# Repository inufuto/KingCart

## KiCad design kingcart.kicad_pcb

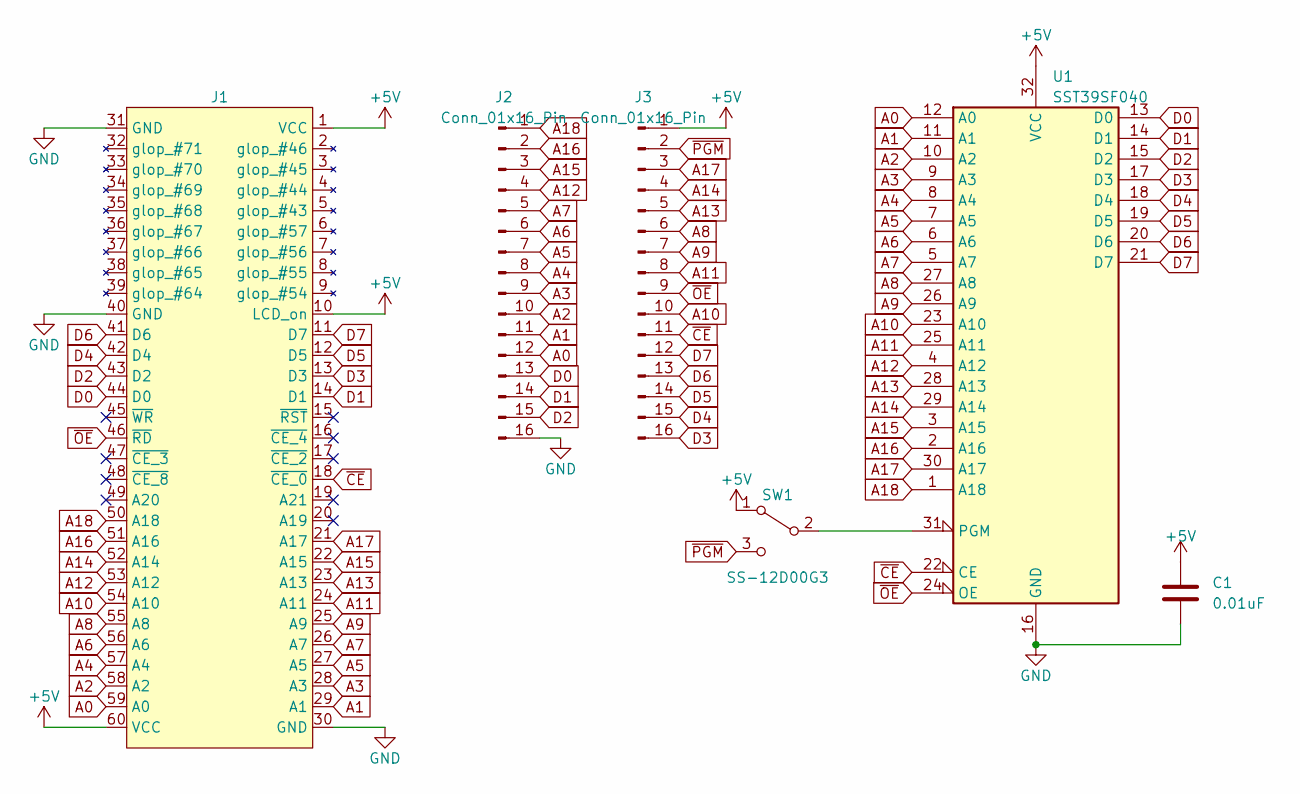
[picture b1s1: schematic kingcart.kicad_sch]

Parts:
C1: 0.01uF; C_Disc_D5.0mm_W2.5mm_P5.00mm
J1: GameKing
J2, J3: Conn_01x16_Pin; PinHeader_1x16_P2.54mm_Vertical
SW1: SS-12D00G3; SlideSW
U1: SST39SF040; PLCC-32_THT-Socket

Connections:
+5V: C1.1, J1.1 (VCC), J1.10 (LCD_on), J1.60 (VCC), J3.1, SW1.1 (A), U1.32 (VCC)
A0: J1.59 (A0), J2.12, U1.12 (A0)
A1: J1.29 (A1), J2.11, U1.11 (A1)
A2: J1.58 (A2), J2.10, U1.10 (A2)
A3: J1.28 (A3), J2.9, U1.9 (A3)
A4: J1.57 (A4), J2.8, U1.8 (A4)
A5: J1.27 (A5), J2.7, U1.7 (A5)
A6: J1.56 (A6), J2.6, U1.6 (A6)
A7: J1.26 (A7), J2.5, U1.5 (A7)
A8: J1.55 (A8), J3.6, U1.27 (A8)
A9: J1.25 (A9), J3.7, U1.26 (A9)
A10: J1.54 (A10), J3.10, U1.23 (A10)
A11: J1.24 (A11), J3.8, U1.25 (A11)
A12: J1.53 (A12), J2.4, U1.4 (A12)
A13: J1.23 (A13), J3.5, U1.28 (A13)
A14: J1.52 (A14), J3.4, U1.29 (A14)
A15: J1.22 (A15), J2.3, U1.3 (A15)
A16: J1.51 (A16), J2.2, U1.2 (A16)
A17: J1.21 (A17), J3.3, U1.30 (A17)
A18: J1.50 (A18), J2.1, U1.1 (A18)
D0: J1.44 (D0), J2.13, U1.13 (D0)
D1: J1.14 (D1), J2.14, U1.14 (D1)
D2: J1.43 (D2), J2.15, U1.15 (D2)
D3: J1.13 (D3), J3.16, U1.17 (D3)
D4: J1.42 (D4), J3.15, U1.18 (D4)
D5: J1.12 (D5), J3.14, U1.19 (D5)
D6: J1.41 (D6), J3.13, U1.20 (D6)
D7: J1.11 (D7), J3.12, U1.21 (D7)
GND: C1.2, J1.30 (GND), J1.31 (GND), J1.40 (GND), J2.16, U1.16 (GND)
unnamed: SW1.2 (B), U1.31 (PGM)
~CE: J1.18 (~CE_0), J3.11, U1.22 (CE)
~OE: J1.46 (~RD), J3.9, U1.24 (OE)
~PGM: J3.2, SW1.3 (C)

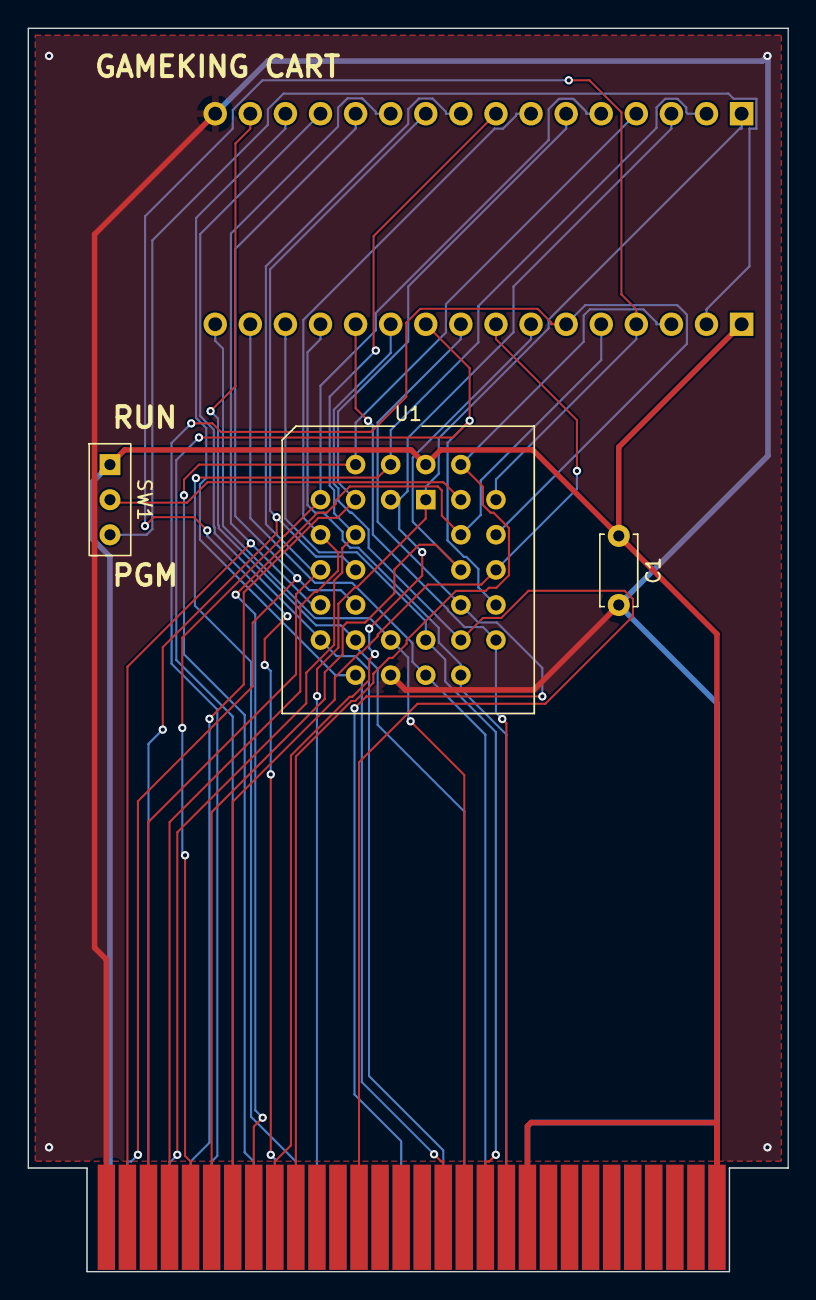
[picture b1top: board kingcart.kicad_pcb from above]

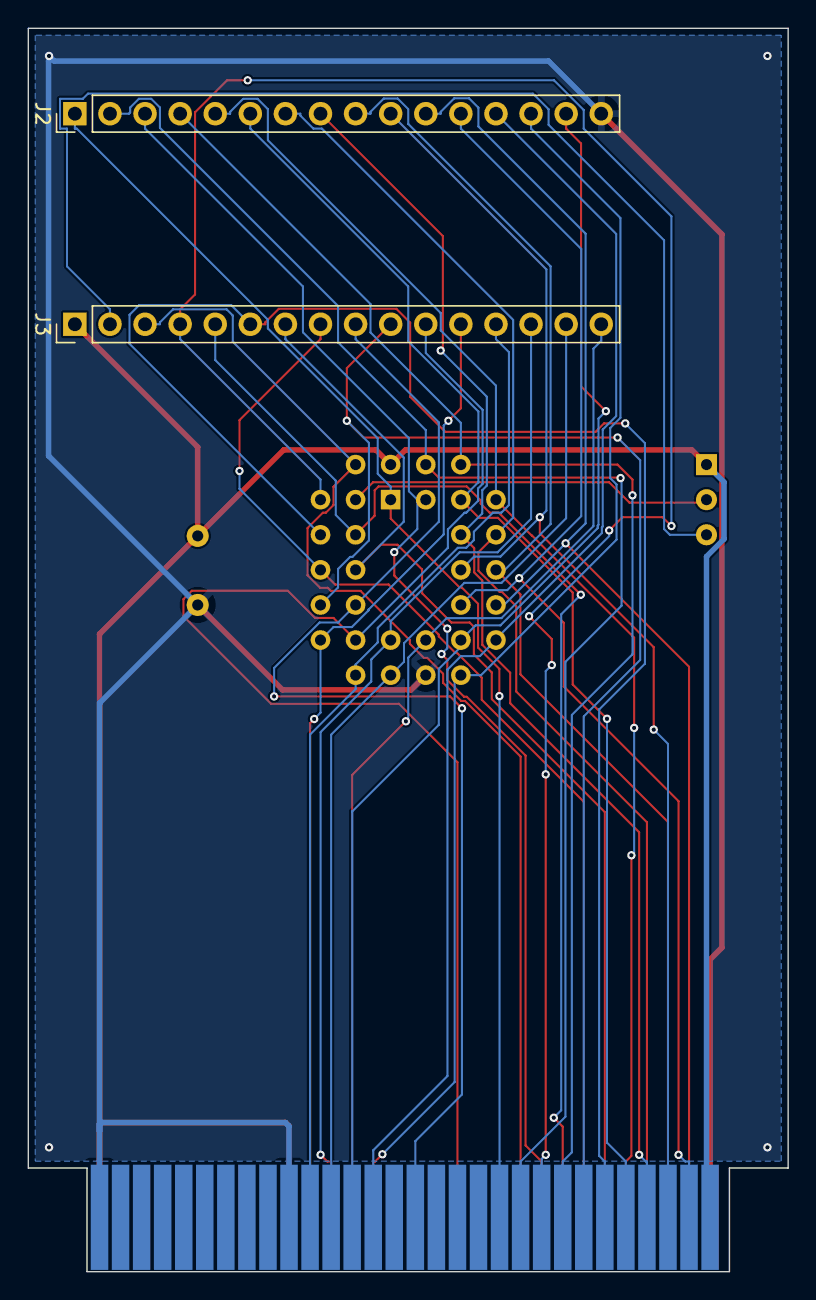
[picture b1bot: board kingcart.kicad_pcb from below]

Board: 2 copper layers, 55.0 x 90.0 mm, 6 parts (2 on the bottom side), 33 nets.

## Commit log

2024-10-02 no message
